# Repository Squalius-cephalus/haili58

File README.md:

# Haili58

Haili58 is a nrf52840 based 58-key column staggered split keyboard. PCB uses hotswap sockets. Design is inspired from REVIUNG41 and Corne keyboards.

PCB is designed for MX and Gateron low profile key switches. The keyboard is designed to be used with a USB dongle.

## [Build Guide](https://github.com/Squalius-cephalus/haili58/wiki/Build-Guide)

## Firmware
Haili58 uses [ZMK firmware.](https://github.com/Squalius-cephalus/haili58_zmk)

TODO:
- RMK Firmware

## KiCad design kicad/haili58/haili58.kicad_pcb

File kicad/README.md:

## Kicad Footprints

This project uses footprints from various repositories

 - [OLED Display 128x32](https://github.com/crides/kleeb/tree/master/display.pretty)
 - [Diode THT/SMD](https://github.com/foostan/kbd) 
 - [Power Switch MSK12C02](https://github.com/joe-scotto/scottokeebs/tree/main/Extras/ScottoKicad)
 - [nice!nano V2](https://github.com/joe-scotto/scottokeebs/tree/main/Extras/ScottoKicad)
 - [GLP Hotswap Socket](https://github.com/siderakb/key-switches.pretty)

Few of the footprints has been edited, those can be found in the **haili_project.pretty** directory.

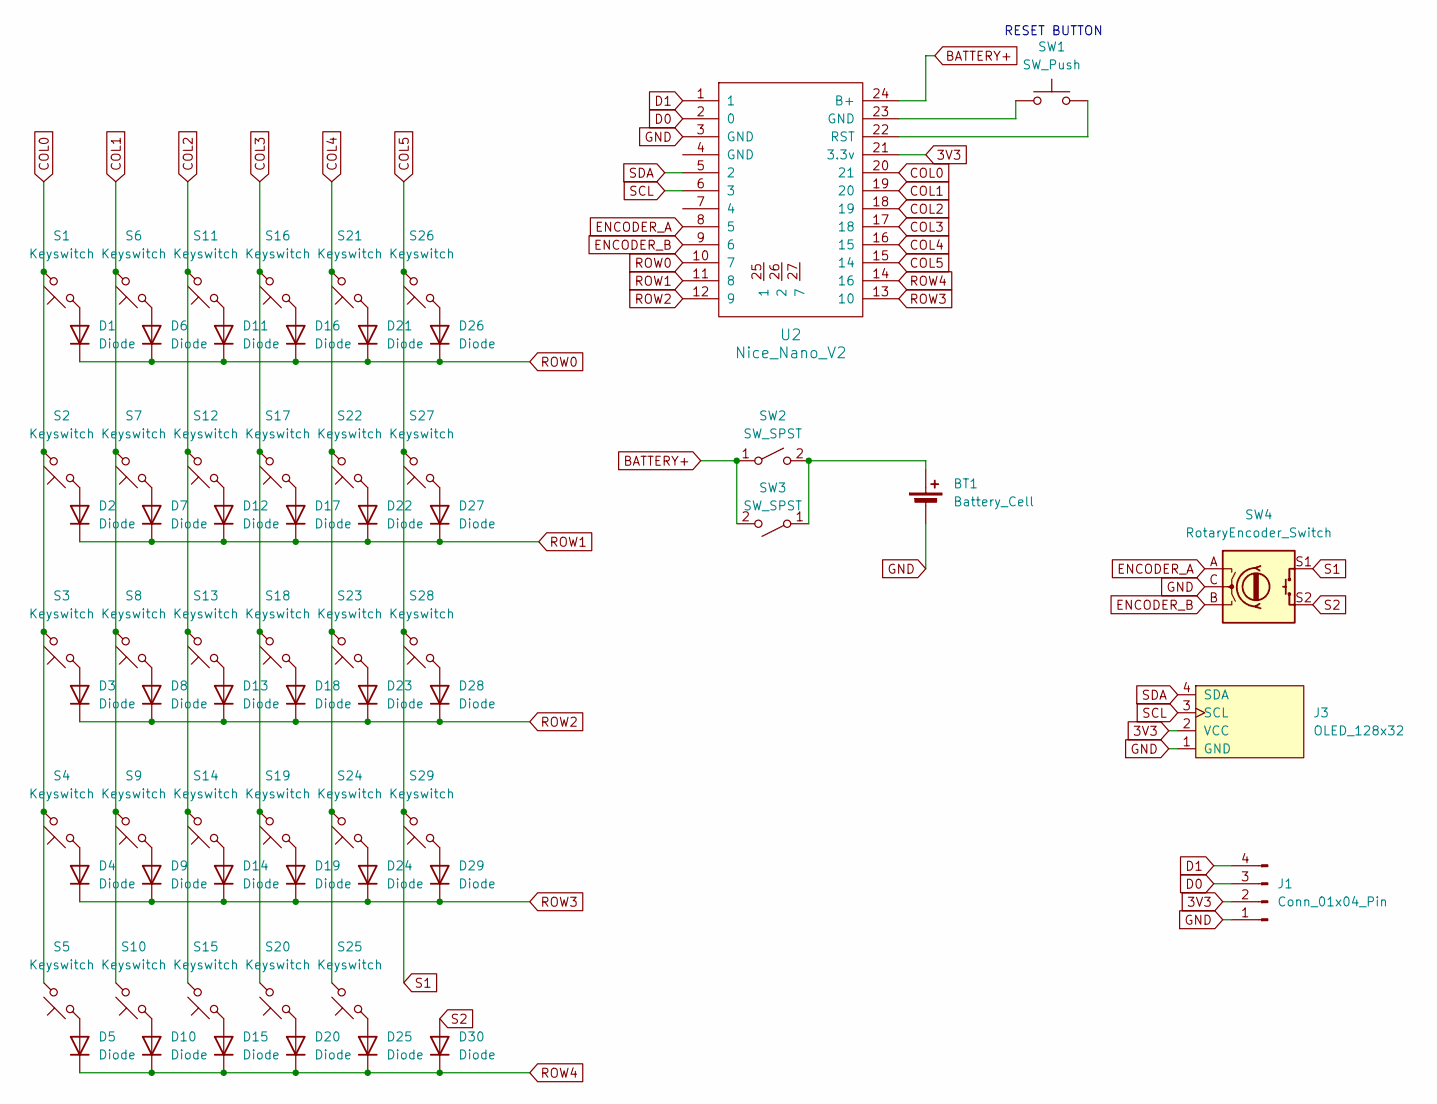
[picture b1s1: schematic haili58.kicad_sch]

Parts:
BT1: Battery_Cell; Battery_Pins_2mm
D1, D2, D3, D4, D5, D6, D7, D8, D9, D10, D11, D12, D13, D14, D15, D16, D17, D18, D19, D20, D21, D22, D23, D24, D25, D26, D27, D28, D29, D30: Diode; D3_TH_SMD_v2
J1: Conn_01x04_Pin; PinSocket_1x04_P2.54mm_Vertical
J3: OLED_128x32; OLED-128x32-double-sided
S1, S2, S3, S4, S5, S6, S7, S8, S9, S10, S11, S12, S13, S14, S15, S16, S17, S18, S19, S20, S21, S22, S23, S24, S25, S26, S27, S28, S29: Keyswitch; SW_Gateron_LowProfile_HotSwap_PTH_edited
SW1: SW_Push; SW_PUSH_6mm_H4.3mm
SW2, SW3: SW_SPST; Switch_MSK12C02
SW4: RotaryEncoder_Switch; RotaryEncoder_Alps_EC11E-Switch_Vertical_H20mm
U2: Nice_Nano_V2; Nice_Nano_V2_edited

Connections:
3V3: J1.2, J3.2 (VCC), U2.21 (3.3v)
BATTERY+: SW2.1 (A), SW3.2 (B), U2.24 (B+)
COL0: S1.2, S2.2, S3.2, S4.2, S5.2, U2.20 (21)
COL1: S6.2, S7.2, S8.2, S9.2, S10.2, U2.19 (20)
COL2: S11.2, S12.2, S13.2, S14.2, S15.2, U2.18 (19)
COL3: S16.2, S17.2, S18.2, S19.2, S20.2, U2.17 (18)
COL4: S21.2, S22.2, S23.2, S24.2, S25.2, U2.16 (15)
COL5: S26.2, S27.2, S28.2, S29.2, SW4.S1, U2.15 (14)
D0: J1.3, U2.2 (0)
D1: J1.4, U2.1
ENCODER_A: SW4.A, U2.8 (5)
ENCODER_B: SW4.B, U2.9 (6)
GND: BT1.2 (-), J1.1, J3.1 (GND), SW4.C, U2.3 (GND)
unnamed: BT1.1 (+), SW2.2 (B), SW3.1 (A)
unnamed: D1.2 (A), S1.1
unnamed: D2.2 (A), S2.1
unnamed: D3.2 (A), S3.1
unnamed: D4.2 (A), S4.1
unnamed: D5.2 (A), S5.1
unnamed: D6.2 (A), S6.1
unnamed: D7.2 (A), S7.1
unnamed: D8.2 (A), S8.1
unnamed: D9.2 (A), S9.1
unnamed: D10.2 (A), S10.1
unnamed: D11.2 (A), S11.1
unnamed: D12.2 (A), S12.1
unnamed: D13.2 (A), S13.1
unnamed: D14.2 (A), S14.1
unnamed: D15.2 (A), S15.1
unnamed: D16.2 (A), S16.1
unnamed: D17.2 (A), S17.1
unnamed: D18.2 (A), S18.1
unnamed: D19.2 (A), S19.1
unnamed: D20.2 (A), S20.1
unnamed: D21.2 (A), S21.1
unnamed: D22.2 (A), S22.1
unnamed: D23.2 (A), S23.1
unnamed: D24.2 (A), S24.1
unnamed: D25.2 (A), S25.1
unnamed: D26.2 (A), S26.1
unnamed: D27.2 (A), S27.1
unnamed: D28.2 (A), S28.1
unnamed: D29.2 (A), S29.1
unnamed: SW1.1, U2.23 (GND)
unnamed: SW1.2, U2.22 (RST)
ROW0: D1.1 (K), D6.1 (K), D11.1 (K), D16.1 (K), D21.1 (K), D26.1 (K), U2.10 (7)
ROW1: D2.1 (K), D7.1 (K), D12.1 (K), D17.1 (K), D22.1 (K), D27.1 (K), U2.11 (8)
ROW2: D3.1 (K), D8.1 (K), D13.1 (K), D18.1 (K), D23.1 (K), D28.1 (K), U2.12 (9)
ROW3: D4.1 (K), D9.1 (K), D14.1 (K), D19.1 (K), D24.1 (K), D29.1 (K), U2.13 (10)
ROW4: D5.1 (K), D10.1 (K), D15.1 (K), D20.1 (K), D25.1 (K), D30.1 (K), U2.14 (16)
S2: D30.2 (A), SW4.S2
SCL: J3.3 (SCL), U2.6 (3)
SDA: J3.4 (SDA), U2.5 (2)

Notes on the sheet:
RESET BUTTON

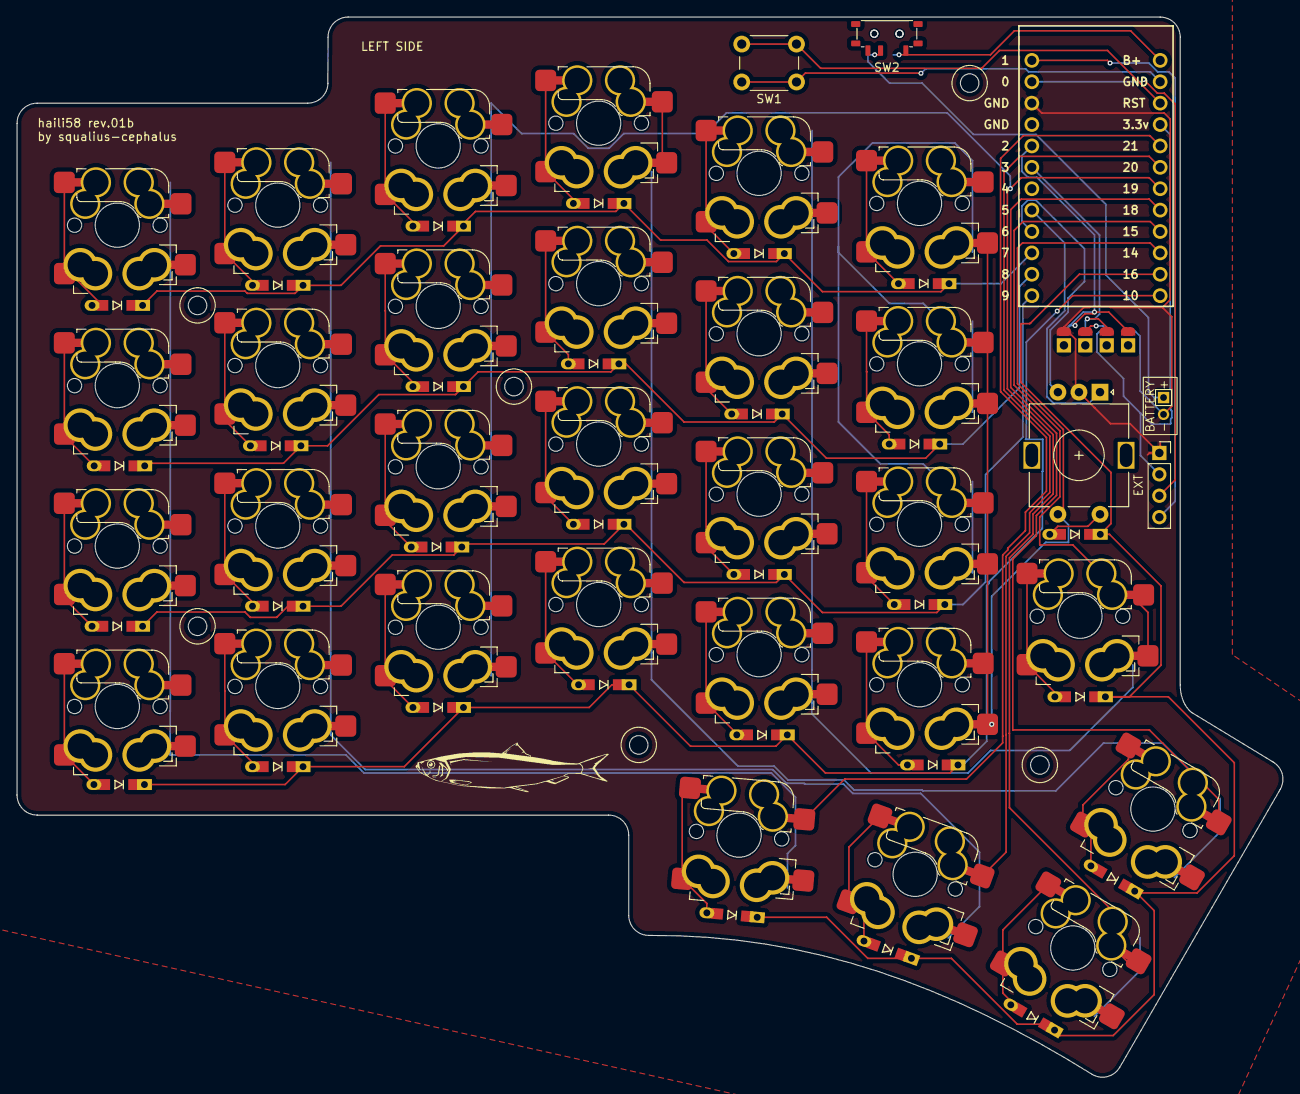
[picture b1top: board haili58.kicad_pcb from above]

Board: 2 copper layers, 150.3 x 125.8 mm, 67 parts (1 on the bottom side), 53 nets.

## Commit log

2026-01-25 STL files, Kicad files etc
2026-01-25 Update and rename FOOTPRINTS.MD to FOOTPRINTS
2026-01-25 Rename FOOTPRINTS to README.md
2026-01-26 Added MX compatible parts
2026-06-08 New case, new README.
